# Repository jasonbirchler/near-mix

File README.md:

# A Near Mix

**Common Denominator Devices 'A Near Mix' Eurorack Module.**

6 input, 2 output minimal panning mixer in 12hp.
Designed for Intellijel 1U format.

A Near Mix is an SMD variant of [Mixor Image][mixor-git], which is built upon the bones of Nearness designed by [Jesper Särnesjö][nearness-git].
Nearness is a product of the *[llllllll][nearness-lines]* community. 

# Changes

* Inputs have been rearranged. Proximity to output now implies strength of panning.
* This module has been re-designed to suit the Intellijel 1U format behind a 12hp panel.
* Resistor values have been changed throughout to give a different stereo image *(An automated method was used for this to select nearest common resistor values based on angle of placement in the stereo field for each input)*
* An additional centre input with a high pass filter has been added so as not to muddy the middle of the stereo field
* Stereo in & out *link* connectors have been added allowing for chaining of multiple modules or linking to other manufacturers' stereo modules without patch cables

# PCB & Panel

KiCad files are provided for the 2 PCB's and a plain panel without artwork.

Gerber files can be found in the Gerbers directory.

# License

In accordance with the wishes of the designer of the work that inspired this, and in the spirit of community development, this work is licensed under a
[Creative Commons Attribution-ShareAlike 4.0 International License][cc-by-sa].

[![CC BY-SA 4.0][cc-by-sa-shield]][cc-by-sa]

[![CC BY-SA 4.0][cc-by-sa-image]][cc-by-sa]

[nearness-lines]: https://llllllll.co/t/prototyping-nearness-a-minimal-panning-mixer-module/8330
[mixor-git]: https://github.com/modular-maculata/mixor-image
[nearness-git]: https://github.com/sarnesjo/nearness
[mi-photo]: https://github.com/modular-maculata/mixor-image/blob/main/mixor-image.jpeg
[cc-by-sa]: http://creativecommons.org/licenses/by-sa/4.0/
[cc-by-sa-image]: https://licensebuttons.net/l/by-sa/4.0/88x31.png
[cc-by-sa-shield]: https://img.shields.io/badge/License-CC%20BY--SA%204.0-lightgrey.svg

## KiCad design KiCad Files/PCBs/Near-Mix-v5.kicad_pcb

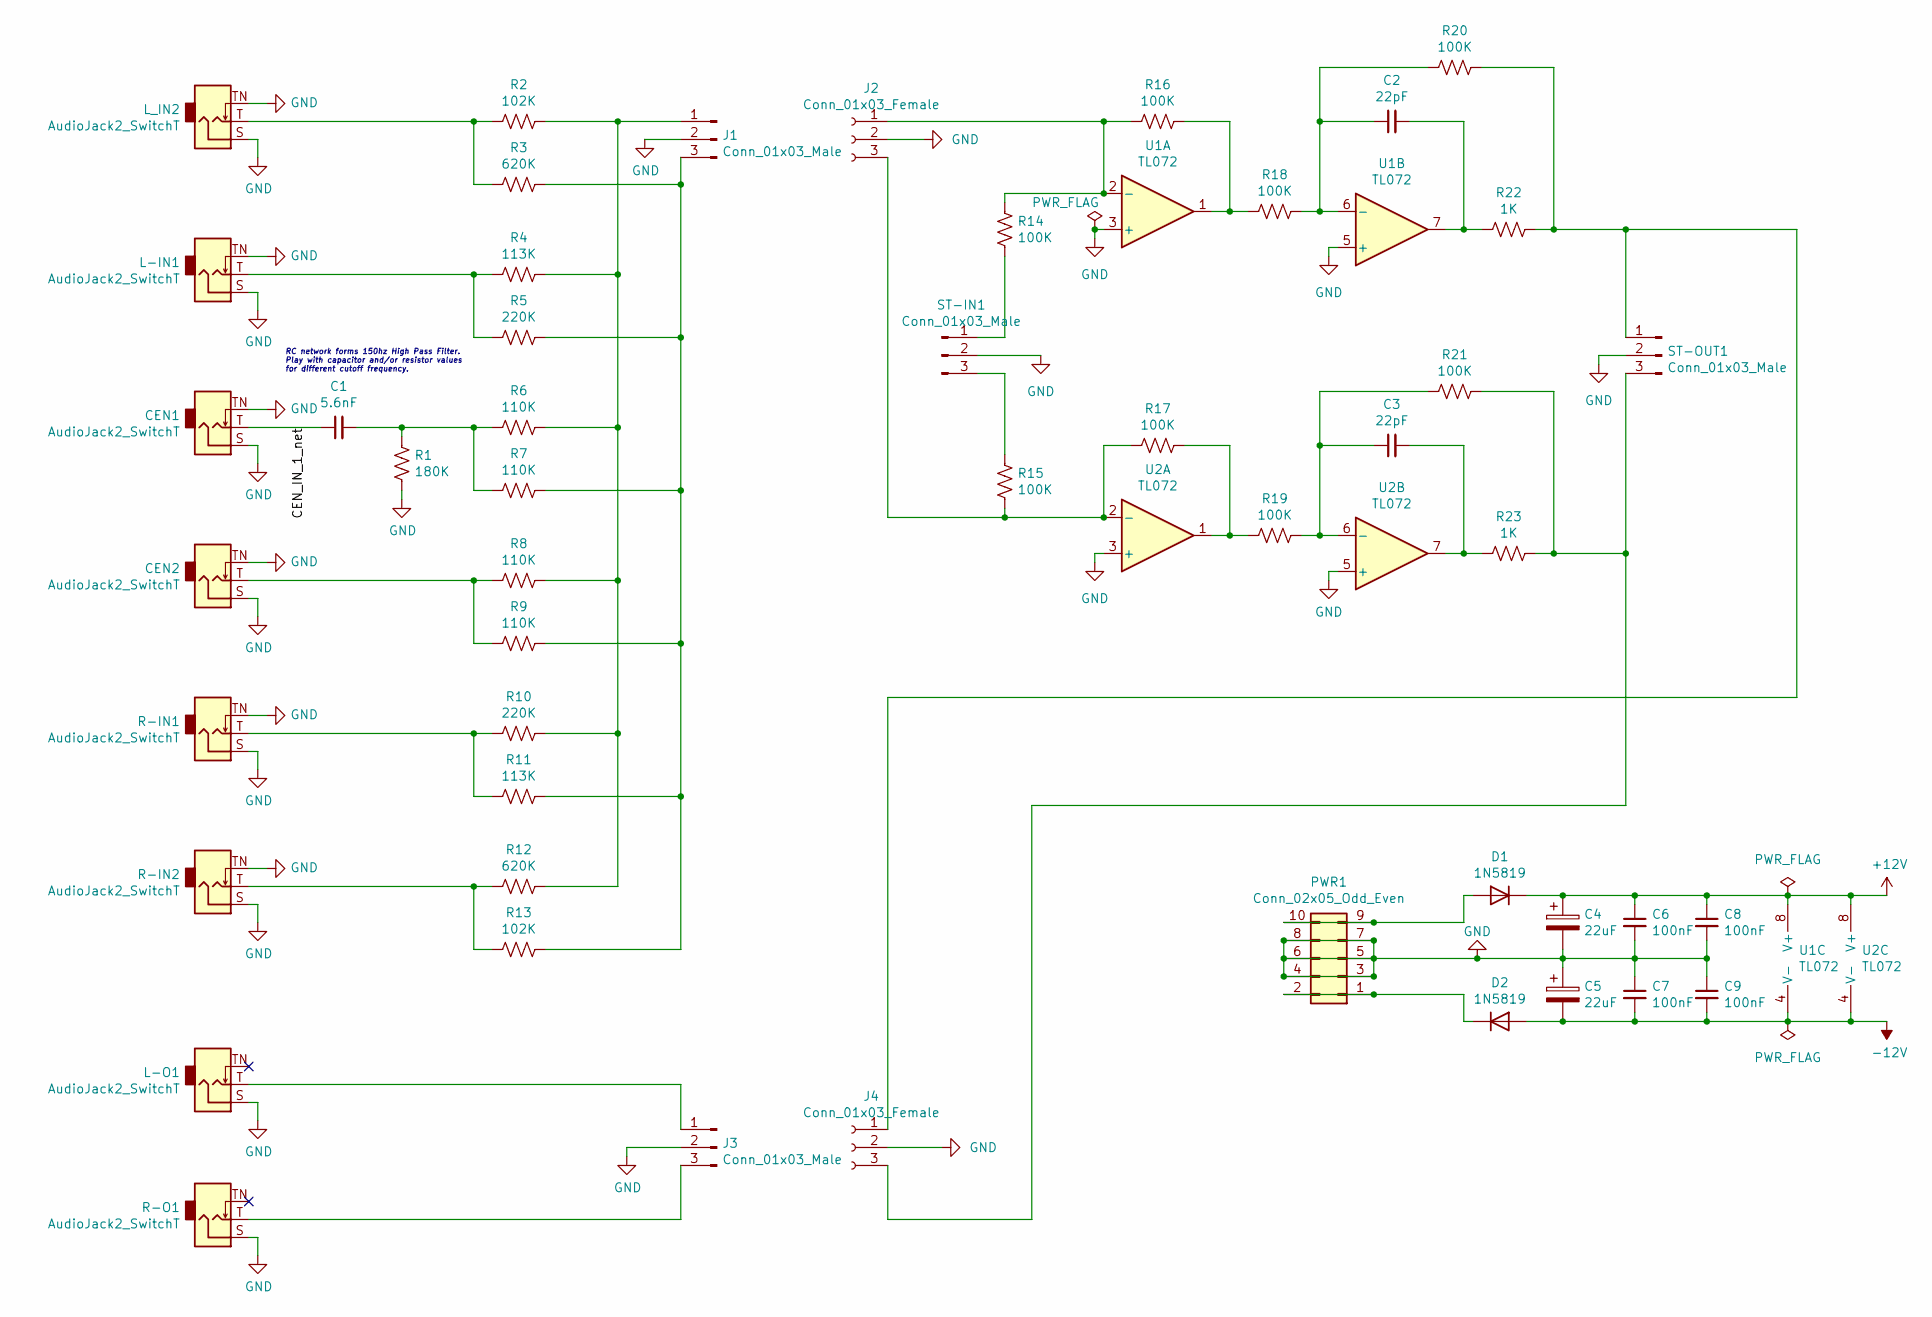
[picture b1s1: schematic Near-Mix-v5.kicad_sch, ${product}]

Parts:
C1: 5.6nF; C_1206_3216Metric
C2, C3: 22pF; C_1206_3216Metric
C4, C5: 22uF; CP_Elec_3x5.3
C6, C7, C8, C9: 100nF; C_1206_3216Metric
CEN1, CEN2: AudioJack2_SwitchT; Jack_3.5mm_QingPu_WQP-PJ398SM_Vertical
D1, D2: 1N5819; D_SOD-123F
J1, J3: Conn_01x03_Male; PinHeader_1x03_P2.54mm_Vertical
J2, J4: Conn_01x03_Female; PinSocket_1x03_P2.54mm_Vertical
L-IN1: AudioJack2_SwitchT; Jack_3.5mm_QingPu_WQP-PJ398SM_Vertical
L-O1: AudioJack2_SwitchT; Jack_3.5mm_QingPu_WQP-PJ398SM_Vertical
L_IN2: AudioJack2_SwitchT; Jack_3.5mm_QingPu_WQP-PJ398SM_Vertical
PWR1: Conn_02x05_Odd_Even; PinHeader_2x05_P2.54mm_Vertical
R1: 180K; R_1206_3216Metric
R2, R13: 102K; R_1206_3216Metric
R3, R12: 620K; R_1206_3216Metric
R4, R11: 113K; R_1206_3216Metric
R5, R10: 220K; R_1206_3216Metric
R6, R7, R8, R9: 110K; R_1206_3216Metric
R14, R15, R16, R17, R18, R19, R20, R21: 100K; R_1206_3216Metric
R22, R23: 1K; R_1206_3216Metric
R-IN1, R-IN2: AudioJack2_SwitchT; Jack_3.5mm_QingPu_WQP-PJ398SM_Vertical
R-O1: AudioJack2_SwitchT; Jack_3.5mm_QingPu_WQP-PJ398SM_Vertical
ST-IN1: Conn_01x03_Male; FanPinHeader_1x03_P2.54mm_Vertical
ST-OUT1: Conn_01x03_Male; FanPinHeader_1x03_P2.54mm_Vertical
U1, U2: TL072; SOIC-8_3.9x4.9mm_P1.27mm

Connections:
+12V: C4.1, C6.1, C8.1, D1.1 (K), U1.8 (V+), U2.8 (V+)
-12V: C5.2, C7.2, C9.2, D2.2 (A), U1.4 (V-), U2.4 (V-)
/CEN_IN_1_net: C1.1, CEN1.T
GND: C4.2, C5.1, C6.2, C7.1, C8.2, C9.1, CEN1.S, CEN1.TN, CEN2.S, CEN2.TN, J1.2, J2.2, J3.2, J4.2, L-IN1.S, L-IN1.TN, L-O1.S, L_IN2.S, L_IN2.TN, PWR1.3, PWR1.4, PWR1.5, PWR1.6, PWR1.7, PWR1.8, R1.2, R-IN1.S, R-IN1.TN, R-IN2.S, R-IN2.TN, R-O1.S, ST-IN1.2, ST-OUT1.2, U1.3 (+), U1.5 (+), U2.3 (+), U2.5 (+)
unnamed: C1.2, R1.1, R6.1, R7.1
unnamed: C2.2, R22.1, U1.7
unnamed: C3.2, R23.1, U2.7
unnamed: CEN2.T, R8.1, R9.1
unnamed: D1.2 (A), PWR1.9, PWR1.10
unnamed: D2.1 (K), PWR1.1, PWR1.2
unnamed: J1.1, R2.2, R4.2, R6.2, R8.2, R10.2, R12.2
unnamed: J1.3, R3.2, R5.2, R7.2, R9.2, R11.2, R13.2
unnamed: J2.1, R14.1, R16.1, U1.2 (-)
unnamed: J2.3, R15.2, R17.1, U2.2 (-)
unnamed: J3.1, L-O1.T
unnamed: J3.3, R-O1.T
unnamed: J4.1, R20.2, R22.2, ST-OUT1.1
unnamed: J4.3, R21.2, R23.2, ST-OUT1.3
unnamed: L-IN1.T, R4.1, R5.1
unnamed: L_IN2.T, R2.1, R3.1
unnamed: R16.2, R18.1, U1.1
unnamed: R17.2, R19.1, U2.1
unnamed: R10.1, R11.1, R-IN1.T
unnamed: R12.1, R13.1, R-IN2.T
unnamed: R14.2, ST-IN1.1
unnamed: R15.1, ST-IN1.3
unnamed: C2.1, R18.2, R20.1, U1.6 (-)
unnamed: C3.1, R19.2, R21.1, U2.6 (-)

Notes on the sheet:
RC network forms 150hz High Pass Filter. Play with capacitor and/or resistor values for different cutoff frequency.

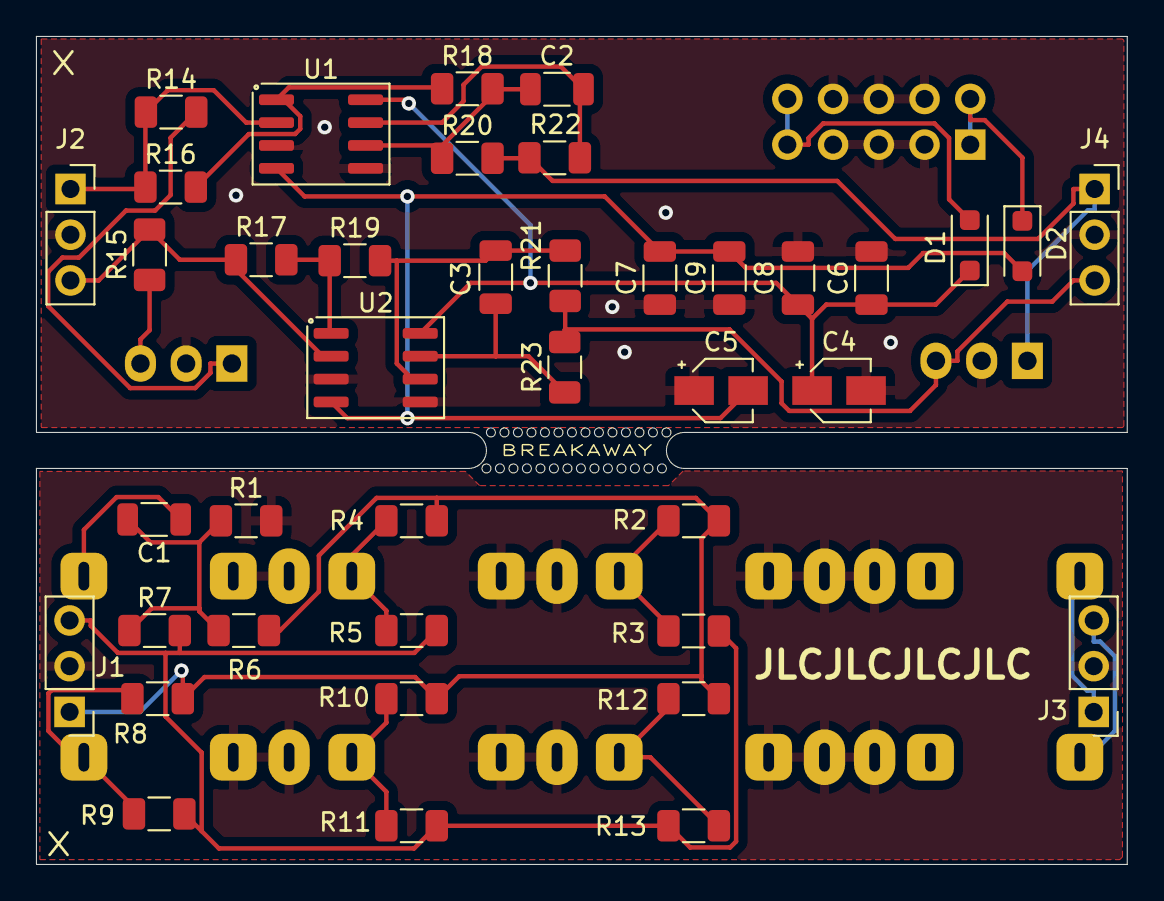
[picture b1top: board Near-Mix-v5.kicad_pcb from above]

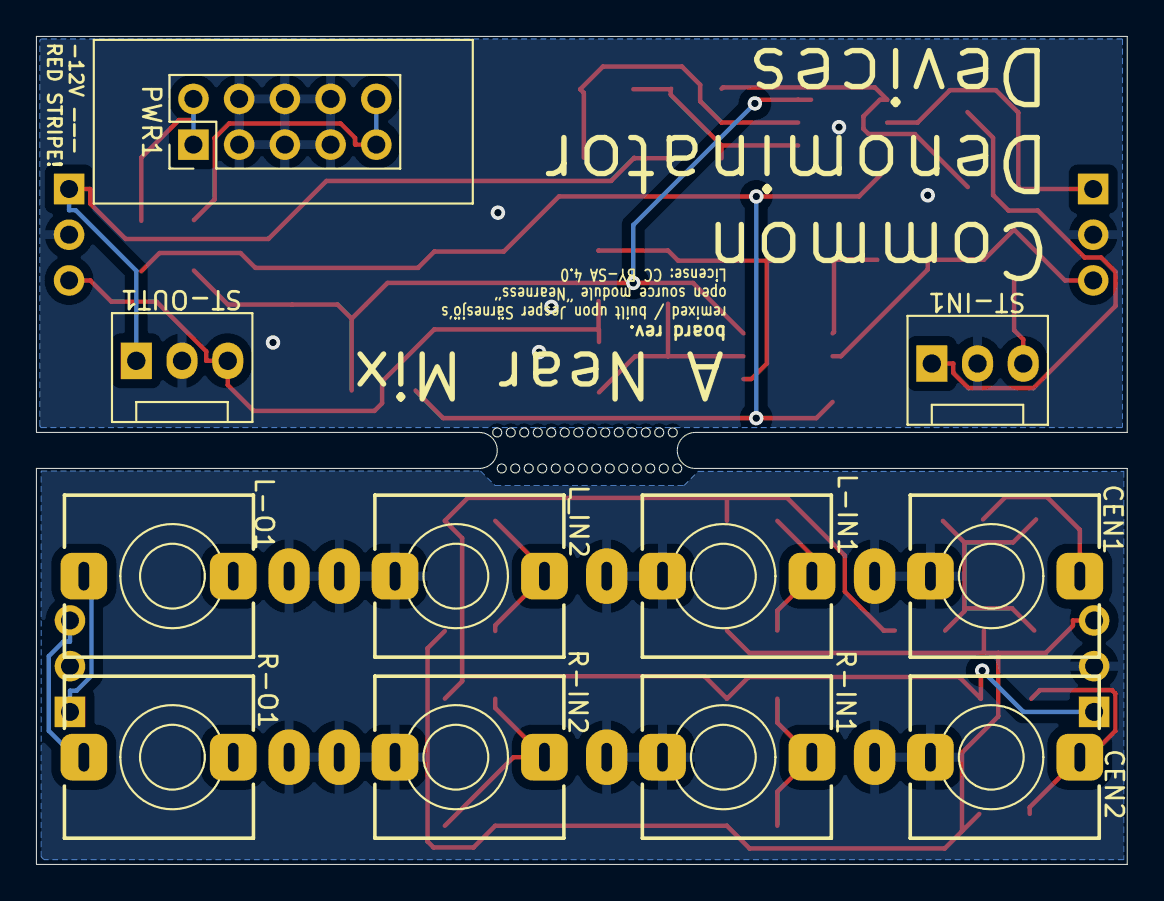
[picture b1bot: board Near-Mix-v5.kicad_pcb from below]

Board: 2 copper layers, 60.6 x 46.0 mm, 79 parts (11 on the bottom side), 28 nets.

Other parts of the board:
MOUSE_BITE_01, MOUSE_BITE_02, MOUSE_BITE_03, MOUSE_BITE_04, MOUSE_BITE_05, MOUSE_BITE_06, MOUSE_BITE_07, MOUSE_BITE_08, MOUSE_BITE_09, MOUSE_BITE_10, MOUSE_BITE_11, MOUSE_BITE_12, MOUSE_BITE_13, MOUSE_BITE_14, MOUSE_BITE_15, MOUSE_BITE_16, MOUSE_BITE_17, MOUSE_BITE_18, MOUSE_BITE_19, MOUSE_BITE_20, MOUSE_BITE_21, MOUSE_BITE_22, MOUSE_BITE_23, MOUSE_BITE_24, MOUSE_BITE_25, MOUSE_BITE_26, MOUSE_BITE_27, MOUSE_BITE_28: 0.5mm_Hole; MountingHole_0.5mm

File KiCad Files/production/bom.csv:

Designator,Footprint,Quantity,Value,LCSC Part #
C1,C_Rect_L4.0mm_W2.0mm_P4.00mm,1,5.6nF,
"C2, C3",C_Disc_D4.0mm_W1.6mm_P3.0mm,2,22pF,
"C4, C5",C_Radial_D5.0mm_H11.0mm_P2.00mm,2,22uF,
"C6, C7, C8, C9",C_Disc_D4.3mm_W1.9mm_P5.00mm,4,100nF,
"CEN1, CEN2, L-IN1, L-O1, L_IN2, R-IN1, R-IN2, R-O1",Jack_3.5mm_QingPu_WQP-PJ398SM_Vertical,8,AudioJack2_SwitchT,
"D1, D2",D_DO-41_SOD81_P7.62mm_Horizontal,2,1N5819,
"J1, J3",PinHeader_1x03_P2.54mm_Vertical,2,Conn_01x03_Male,
"J2, J4",PinSocket_1x03_P2.54mm_Vertical,2,Conn_01x03_Female,
PWR1,IDC-Header_2x05_P2.54mm_Vertical,1,Conn_02x05_Odd_Even,
R1,R_Axial_DIN0204_L3.6mm_D1.6mm_P5.08mm_Horizontal,1,180K,
"R10, R5",R_Axial_DIN0204_L3.6mm_D1.6mm_P7.62mm_Horizontal,2,220K,
"R11, R4",R_Axial_DIN0204_L3.6mm_D1.6mm_P7.62mm_Horizontal,2,113K,
"R12, R3",R_Axial_DIN0204_L3.6mm_D1.6mm_P7.62mm_Horizontal,2,620K,
"R13, R2",R_Axial_DIN0204_L3.6mm_D1.6mm_P7.62mm_Horizontal,2,102K,
"R14, R15, R16, R17, R18, R19, R20, R21",R_Axial_DIN0204_L3.6mm_D1.6mm_P5.08mm_Horizontal,8,100K,
"R22, R23",R_Axial_DIN0204_L3.6mm_D1.6mm_P5.08mm_Horizontal,2,1K,
"R6, R7, R8, R9",R_Axial_DIN0204_L3.6mm_D1.6mm_P7.62mm_Horizontal,4,110K,
"ST-IN1, ST-OUT1",FanPinHeader_1x03_P2.54mm_Vertical,2,Conn_01x03_Male,
"U1, U2",DIP-8_W7.62mm_Socket,2,TL072,

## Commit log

2023-11-23 fix all missing symbols and update to KiCad7 project
2023-11-24 remove Modular Maculata branding
2023-11-28 only 1 error committing before flipping components so all SMD are on the same side
2024-06-09 add gitignore
2024-06-09 fix missing symbols and eeschema errors
2024-06-09 fix gitignore
2024-06-09 remove Modular Maculata graphics
2024-06-09 adds C/D logo, change resistors to SMD
2024-06-09 ignore production dir
2024-06-09 removing production directory so that its contents will be ignored
2024-06-09 updated panel with C/D graphics
2024-06-09 PCB cleanup
2024-06-09 remove Gerber Files dir
2024-06-09 creates separate directories for PCBs and panel brings panel layout back from the dead
2024-06-09 version submitted to JLCPCB 2024-06-09
2024-10-23 remove build guide and update README
2024-10-23 rename Kicad files and update schematic info
2024-10-25 first fully SMD version ordered from JLCPCB 2024-10-24
2024-10-25 uses different footprint for diodes - JLC didn't have parts to match previous updates labels so they are oriented sanely and not cut off by pads ordered 2024-10-25 order for previous commit cancelled

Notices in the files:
KiCad Files/PCBs/Near-Mix-v5.kicad_pcb:
License: CC BY-SA 4.0
